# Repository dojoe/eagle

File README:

Some Eagle projects I am or have been working on.

  Atmega32U4-Breakout   - A breakout board for the Atmega32U4 uC

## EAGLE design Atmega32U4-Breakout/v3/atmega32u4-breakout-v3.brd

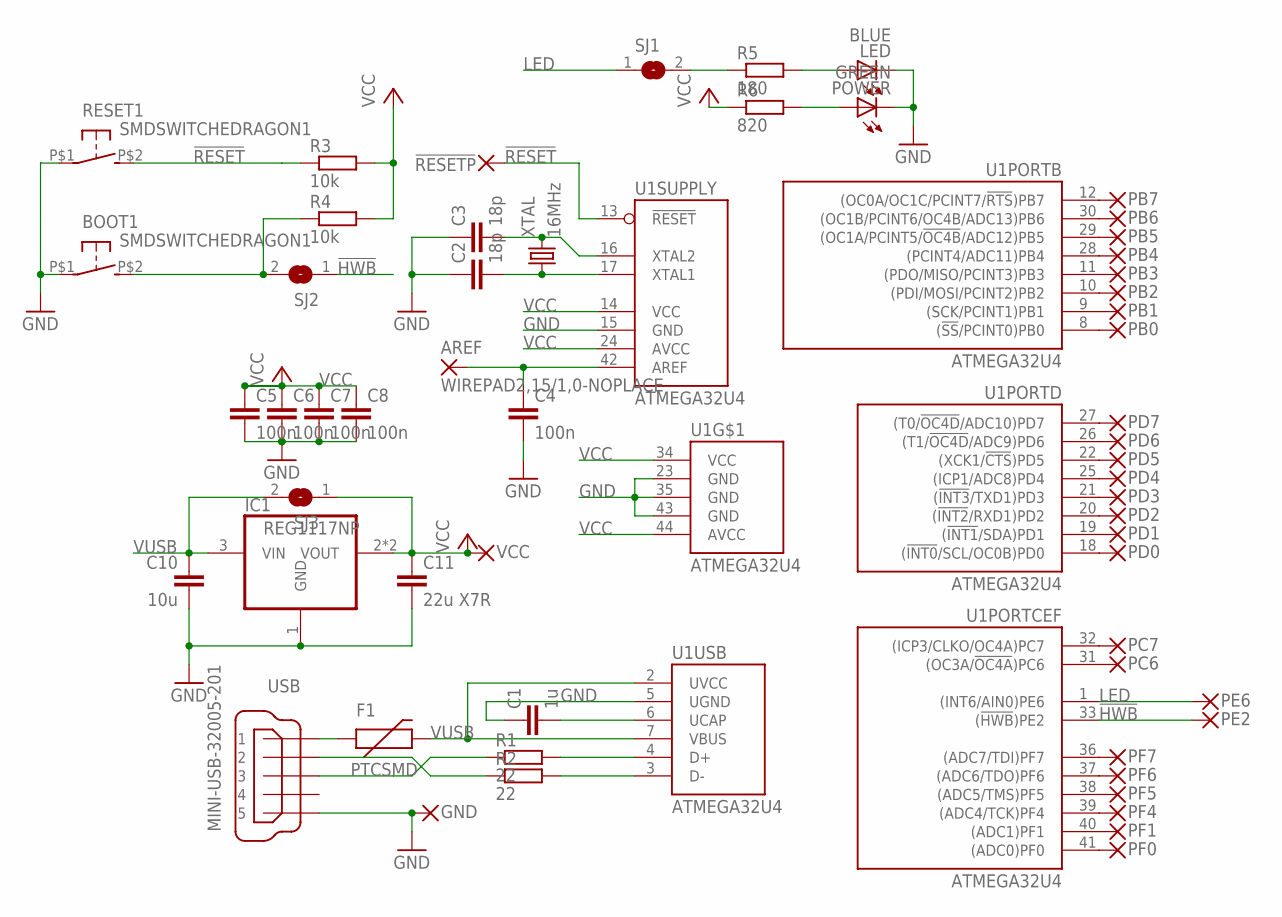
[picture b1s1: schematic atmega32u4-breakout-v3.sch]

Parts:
!RESETP: WIREPAD2,15/1,0-NOPLACE; 2,15/1,0-NOPLACE
AREF: WIREPAD2,15/1,0-NOPLACE; 2,15/1,0-NOPLACE
BOOT1: SMDSWITCHEDRAGON1; EDRAGON1
C1: 1u; C0603
C2, C3: 18p; C0603
C4, C5, C6, C7, C8: 100n; C0603
C10: 10u; C0805K
C11: 22u X7R; C1206K
F1: PTCSMD; PTC-1206
GND: WIREPAD2,15/1,0-NOPLACE; 2,15/1,0-NOPLACE
IC1: REG1117NP; SOT223-NP
LED: BLUE; CHIPLED_0805
PB0, PB1, PB2, PB3, PB4, PB5, PB6, PB7: WIREPAD2,15/1,0-NOPLACE; 2,15/1,0-NOPLACE
PC6, PC7: WIREPAD2,15/1,0-NOPLACE; 2,15/1,0-NOPLACE
PD0, PD1, PD2, PD3, PD4, PD5, PD6, PD7: WIREPAD2,15/1,0-NOPLACE; 2,15/1,0-NOPLACE
PE2, PE6: WIREPAD2,15/1,0-NOPLACE; 2,15/1,0-NOPLACE
PF0, PF1, PF4, PF5, PF6, PF7: WIREPAD2,15/1,0-NOPLACE; 2,15/1,0-NOPLACE
POWER: GREEN; CHIPLED_0805
R1, R2: 22; R0603
R3, R4: 10k; R0603
R5: 180; R0603
R6: 820; R0603
RESET1: SMDSWITCHEDRAGON1; EDRAGON1
SJ1, SJ2: SJ
SJ3: SJNP
U1: ATMEGA32U4; TQFP44
USB: MINI-USB-32005-201; 32005-201
VCC: WIREPAD2,15/1,0-NOPLACE; 2,15/1,0-NOPLACE
XTAL: 16MHz; ABM7

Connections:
!HWB: PE2.1, SJ2.1, U1.33 ((!HWB!)PE2)
!RESET: !RESETP.1, R3.1, RESET1.P$2 (S), U1.13 (!RESET)
AREF: AREF.1, C4.1, U1.42 (AREF)
GND: BOOT1.P$1, C1.1, C2.1, C3.1, C4.2, C5.2, C6.2, C7.2, C8.2, C10.2, C11.2, GND.1, IC1.1 (GND), LED.C, POWER.C, RESET1.P$1, U1.5 (UGND), U1.15 (GND), U1.23 (GND), U1.35 (GND), U1.43 (GND), USB.5
LED: PE6.1, SJ1.1, U1.1 ((INT6/AIN0)PE6)
MISO: PB3.1, U1.11 ((PDO/MISO/PCINT3)PB3)
MOSI: PB2.1, U1.10 ((PDI/MOSI/PCINT2)PB2)
unnamed: R1.1, USB.3
unnamed: R2.1, USB.2
unnamed: PB0.1, U1.8 ((!SS!/PCINT0)PB0)
unnamed: F1.1, USB.1
unnamed: C2.2, U1.17 (XTAL1), XTAL.P$1 (1)
unnamed: C3.2, U1.16 (XTAL2), XTAL.P$2 (2)
unnamed: C1.2, U1.6 (UCAP)
unnamed: POWER.A, R6.2
unnamed: R1.2, U1.4 (D+)
unnamed: R2.2, U1.3 (D-)
unnamed: R5.1, SJ1.2
unnamed: PD5.1, U1.22 ((XCK1/!CTS!)PD5)
unnamed: PB4.1, U1.28 ((PCINT4/ADC11)PB4)
unnamed: PB5.1, U1.29 ((OC1A/PCINT5/!OC4B!/ADC12)PB5)
unnamed: PF0.1, U1.41 ((ADC0)PF0)
unnamed: PF1.1, U1.40 ((ADC1)PF1)
unnamed: PF4.1, U1.39 ((ADC4/TCK)PF4)
unnamed: PF5.1, U1.38 ((ADC5/TMS)PF5)
unnamed: PF6.1, U1.37 ((ADC6/TDO)PF6)
unnamed: PF7.1, U1.36 ((ADC7/TDI)PF7)
unnamed: BOOT1.P$2 (S), R4.1, SJ2.2
unnamed: LED.A, R5.2
unnamed: PC6.1, U1.31 ((OC3A/!OC4A!)PC6)
unnamed: PC7.1, U1.32 ((ICP3/CLKO/OC4A)PC7)
unnamed: PB6.1, U1.30 ((OC1B/PCINT6/OC4B/ADC13)PB6)
unnamed: PB7.1, U1.12 ((OC0A/OC1C/PCINT7/!RTS!)PB7)
unnamed: PD0.1, U1.18 ((!INT0!/SCL/OC0B)PD0)
unnamed: PD1.1, U1.19 ((!INT1!/SDA)PD1)
unnamed: PD2.1, U1.20 ((!INT2!/RXD1)PD2)
unnamed: PD3.1, U1.21 ((!INT3!/TXD1)PD3)
unnamed: PD4.1, U1.25 ((ICP1/ADC8)PD4)
unnamed: PD6.1, U1.26 ((T1/!OC4D!/ADC9)PD6)
unnamed: PD7.1, U1.27 ((T0/!OC4D!/ADC10)PD7)
SCK: PB1.1, U1.9 ((SCK/PCINT1)PB1)
VCC: C5.1, C6.1, C7.1, C8.1, C11.1, IC1.2 (VOUT), IC1.4 (VOUT), R3.2, R4.2, R6.1, SJ3.1, U1.14 (VCC), U1.24 (AVCC), U1.34 (VCC), U1.44 (AVCC), VCC.1
VUSB: C10.1, F1.2, IC1.3 (VIN), SJ3.2, U1.2 (UVCC), U1.7 (VBUS)

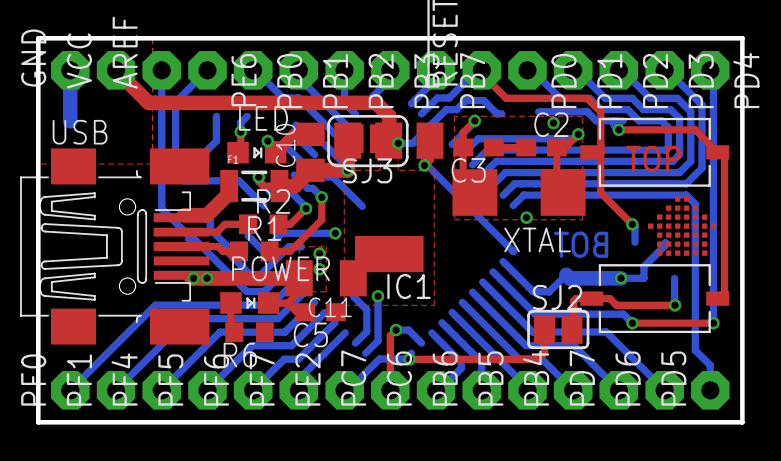
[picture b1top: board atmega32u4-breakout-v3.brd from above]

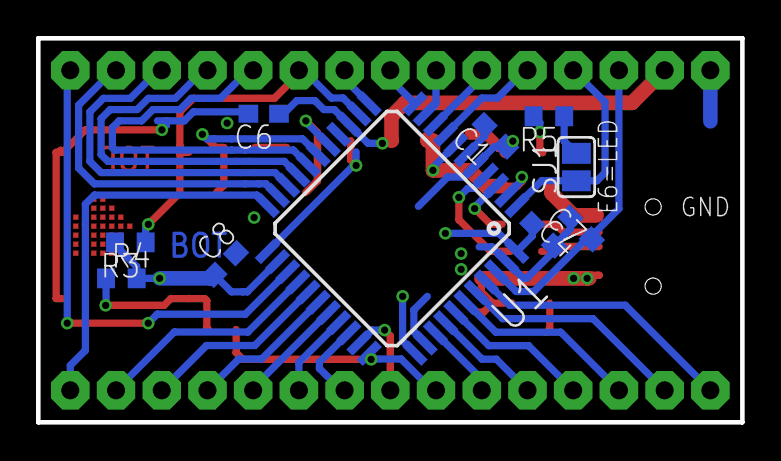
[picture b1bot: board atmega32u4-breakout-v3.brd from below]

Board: 2 copper layers, 39.1 x 21.3 mm, 58 parts (10 on the bottom side), 43 nets.

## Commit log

2012-01-12 Initial commit, add v1 and v2 of the Atmega32U4 Breakout
2012-01-12 Ignore Eagle's backup files
2012-01-12 Add double-sided v3 of the ATmega32U4 board
2012-02-11 - Add silkscreen line between LED resistors so their orientation becomes more clear. - Change green LED resistor to 150R - Change input filter cap to 0805 4.7uF - Match BOM
2012-02-11 Add assembly instructions
2012-02-15 Update name to "TinyMega" in instructions
2012-03-10 Update instructions with solder jumpers
2012-03-10 Straighten a few bits of the layout, adapt to switches with ground pin. Also, match BOM.
2014-04-26 TinyMega v2 with optional 3V3 supply
2014-04-26 Change LED silkscreen for more clarity
2014-05-17 Change button model, make vias smaller, adapt to multi-circuit-boards design rules, lots of small routing changes
2014-05-17 change USB plug package, rearrange bottom solder jumper
2014-05-17 Add resettable fuse, rearrange stuff
2014-06-09 Update BOM with more Digi-Key part numbers
2014-07-09 Add TOP and BOT markers, shuffle some things around
2014-07-21 Nudge some more stuff around, change silkscreen, add large GND pad on bottom, add multicb gerber job
2014-07-21 Add TinyMega Eagle part for easy inclusion in own projects
2014-07-21 Add dimension output to Gerber job
2014-09-21 Change red LED to blue, adapt dropper resistor
2014-09-21 Update assembly instructions for new board
2014-10-02 Instructions: Swap crystal and regulator steps, add Wiki link

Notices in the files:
parts and their libraries:
SparkFun-PowerIC: Licensing: Creative Commons ShareAlike 4.0 International - https://creativecommons.org/licenses/by-sa/4.0
